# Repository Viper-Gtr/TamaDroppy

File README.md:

# TamaDroppy
 Digital Egg Drop Egg - original from /CNCKitchen/TamaDroppy
 
I wanted to make such an egg for a long time, but Stefan was quicker.

So here is my custom PCB and CAD-files. It a little bit differnet assambeled, but the same screen position and external dimensions.

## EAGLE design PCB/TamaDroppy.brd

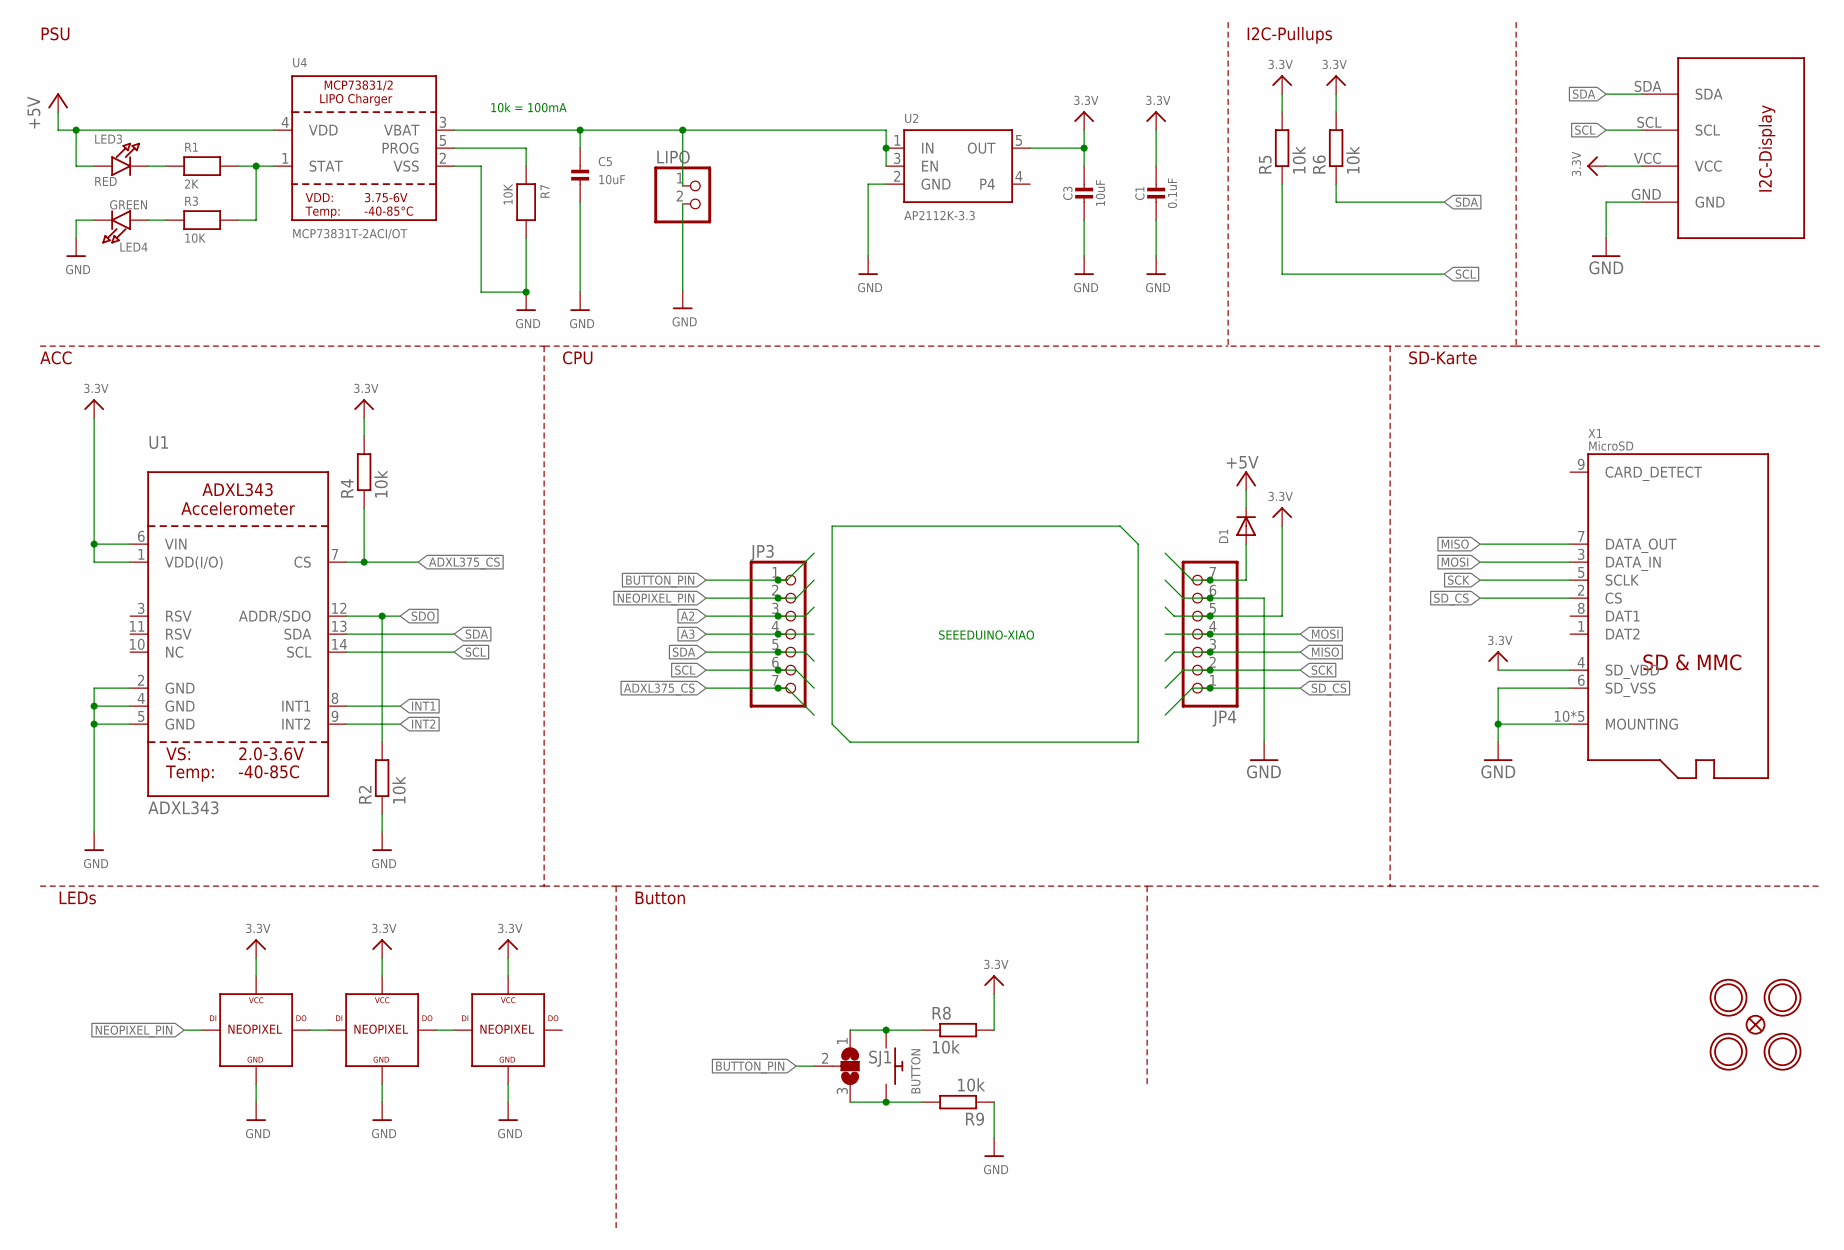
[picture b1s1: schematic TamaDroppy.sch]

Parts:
BUTTON: SWITCH_PUSHBUTTONC&K_KSS; BTN_CK_KSS
C1: 0.1uF; 0603-NO
C3, C5: 10uF; 0805-NO
D1: DIODESOD-323F; SOD-323F
FID3: FIDUCIAL_1MM
JP3, JP4: HEADER-1X7THICKER; 1X07_ROUND_76
LED3: RED; CHIPLED_0603_NOOUTLINE
LED4: GREEN; CHIPLED_0603_NOOUTLINE
LIPO: PINHD-1X2; 1X02
R1: 2K; 0603-NO
R2, R4, R5, R6, R8, R9: 10k; M0805
R3, R7: 10K; 0603-NO
SJ1: SJ2W; SJ_2
U1: ADXL343; LGA14
U2: AP2112K-3.3; SOT23-5
U4: MCP73831T-2ACI/OT; SOT23-5
U$2, U$17, U$19, U$21: MOUNTINGHOLE2.5; MOUNTINGHOLE_2.5_PLATED
U$16: EASTRISING_0.66
U$31, U$32, U$33: WS2812_BOB; WS2812B
X1: MicroSD; MOLEX_104031-0811

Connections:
3.3V: C1.1, C3.1, JP4.5, R4.2, R5.2, R6.2, R8.2, U1.1 (VDD(I/O)), U1.6 (VIN), U2.5 (OUT), U$16.VCC, U$31.VCC1 (VCC), U$31.VCC2 (VCC), U$32.VCC1 (VCC), U$32.VCC2 (VCC), U$33.VCC1 (VCC), U$33.VCC2 (VCC), X1.4 (SD_VDD)
+5V: D1.C, LED3.A, U4.4 (VDD)
A2: JP3.3
A3: JP3.4
ADXL375_CS: JP3.7, R4.1, U1.7 (CS)
BUTTON_PIN: JP3.1, SJ1.2
GND: C1.2, C3.2, C5.2, JP4.6, LED4.C, LIPO.2, R2.1, R7.2, R9.1, U1.2 (GND), U1.4 (GND), U1.5 (GND), U2.2 (GND), U4.2 (VSS), U$16.GND, U$31.GND1 (GND), U$31.GND2 (GND), U$32.GND1 (GND), U$32.GND2 (GND), U$33.GND1 (GND), U$33.GND2 (GND), X1.6 (SD_VSS), X1.10 (MOUNTING), X1.G1 (MOUNTING), X1.G2 (MOUNTING), X1.G3 (MOUNTING), X1.G4 (MOUNTING)
INT1: U1.8 (INT1)
INT2: U1.9 (INT2)
MISO: JP4.3, X1.7 (DATA_OUT)
MOSI: JP4.4, X1.3 (DATA_IN)
unnamed: LED3.C, R1.1
unnamed: R1.2, R3.2, U4.1 (STAT)
unnamed: R7.1, U4.5 (PROG)
unnamed: D1.A, JP4.7
unnamed: LED4.A, R3.1
unnamed: BUTTON.P$1, R8.1, SJ1.1
unnamed: BUTTON.P$2, R9.2, SJ1.3
unnamed: U$31.DOUT (DO), U$32.DIN (DI)
unnamed: U$32.DOUT (DO), U$33.DIN (DI)
NEOPIXEL_PIN: JP3.2, U$31.DIN (DI)
SCK: JP4.2, X1.5 (SCLK)
SCL: JP3.6, R5.1, U1.14 (SCL), U$16.SCL
SDA: JP3.5, R6.1, U1.13 (SDA), U$16.SDA
SDO: R2.2, U1.12 (ADDR/SDO)
SD_CS: JP4.1, X1.2 (CS)
VBAT1: C5.1, LIPO.1, U2.1 (IN), U2.3 (EN), U4.3 (VBAT)

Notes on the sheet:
10k = 100mA
SEEEDUINO-XIAO
I2C-Pullups
PSU
ACC
CPU
SD-Karte
Button
LEDs

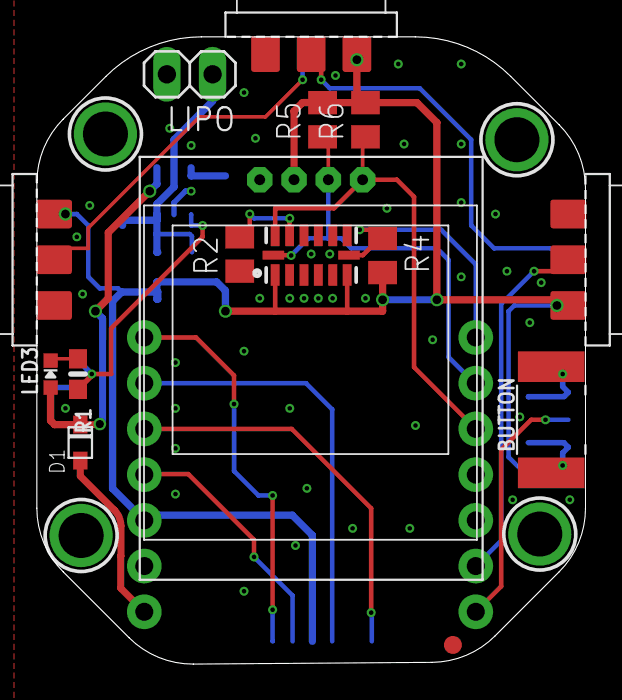
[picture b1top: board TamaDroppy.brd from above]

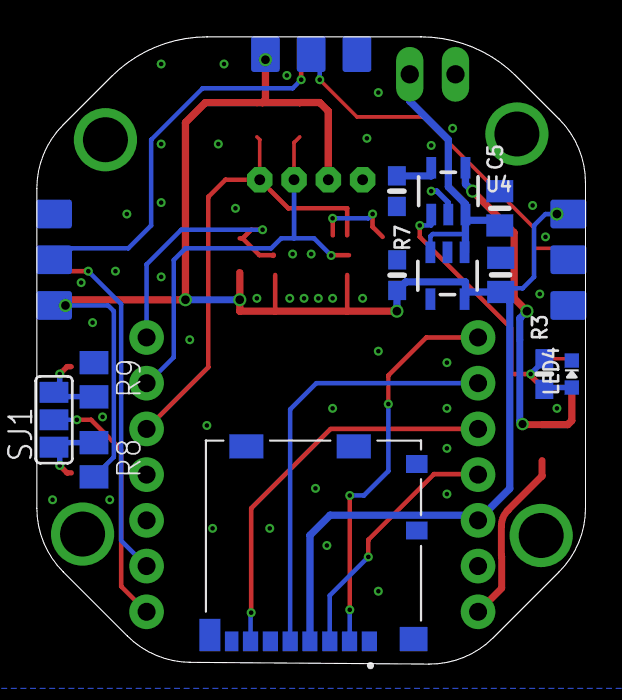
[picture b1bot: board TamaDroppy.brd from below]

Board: 2 copper layers, 30.5 x 34.8 mm, 33 parts (12 on the bottom side), 23 nets.

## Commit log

2023-07-03 Add files via upload
    Updated Version with an custom PCB

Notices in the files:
parts and their libraries:
microbuilder: This work is placed in the public domain, and may be freely used for commercial and non-commercial work with the following conditions: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
